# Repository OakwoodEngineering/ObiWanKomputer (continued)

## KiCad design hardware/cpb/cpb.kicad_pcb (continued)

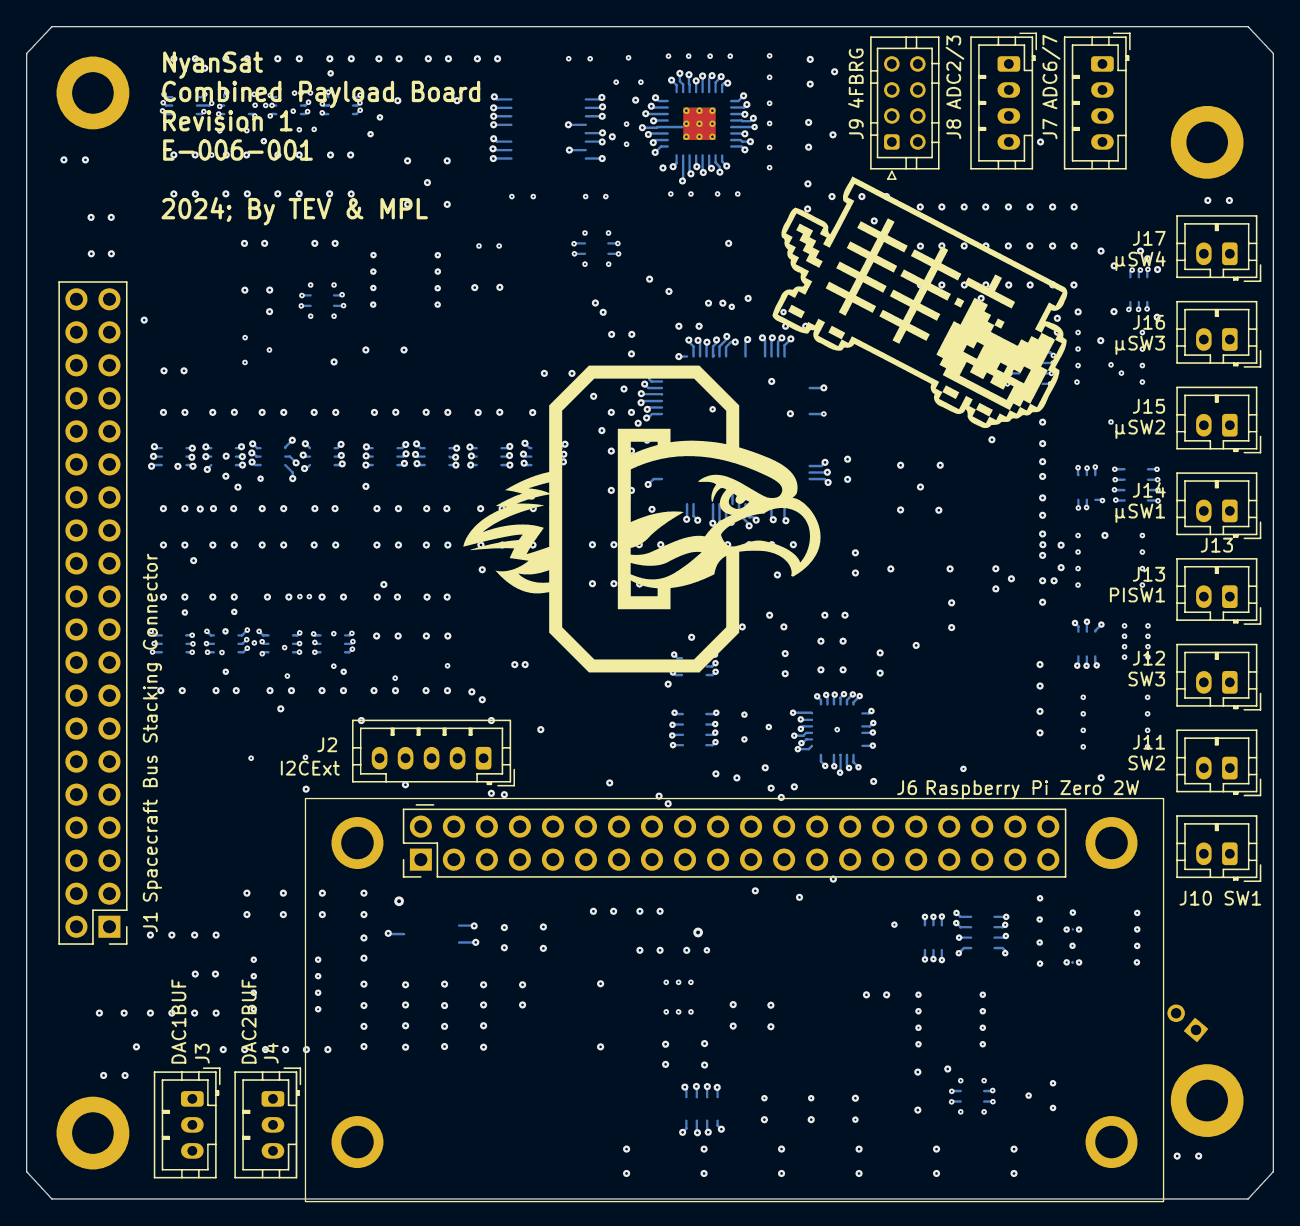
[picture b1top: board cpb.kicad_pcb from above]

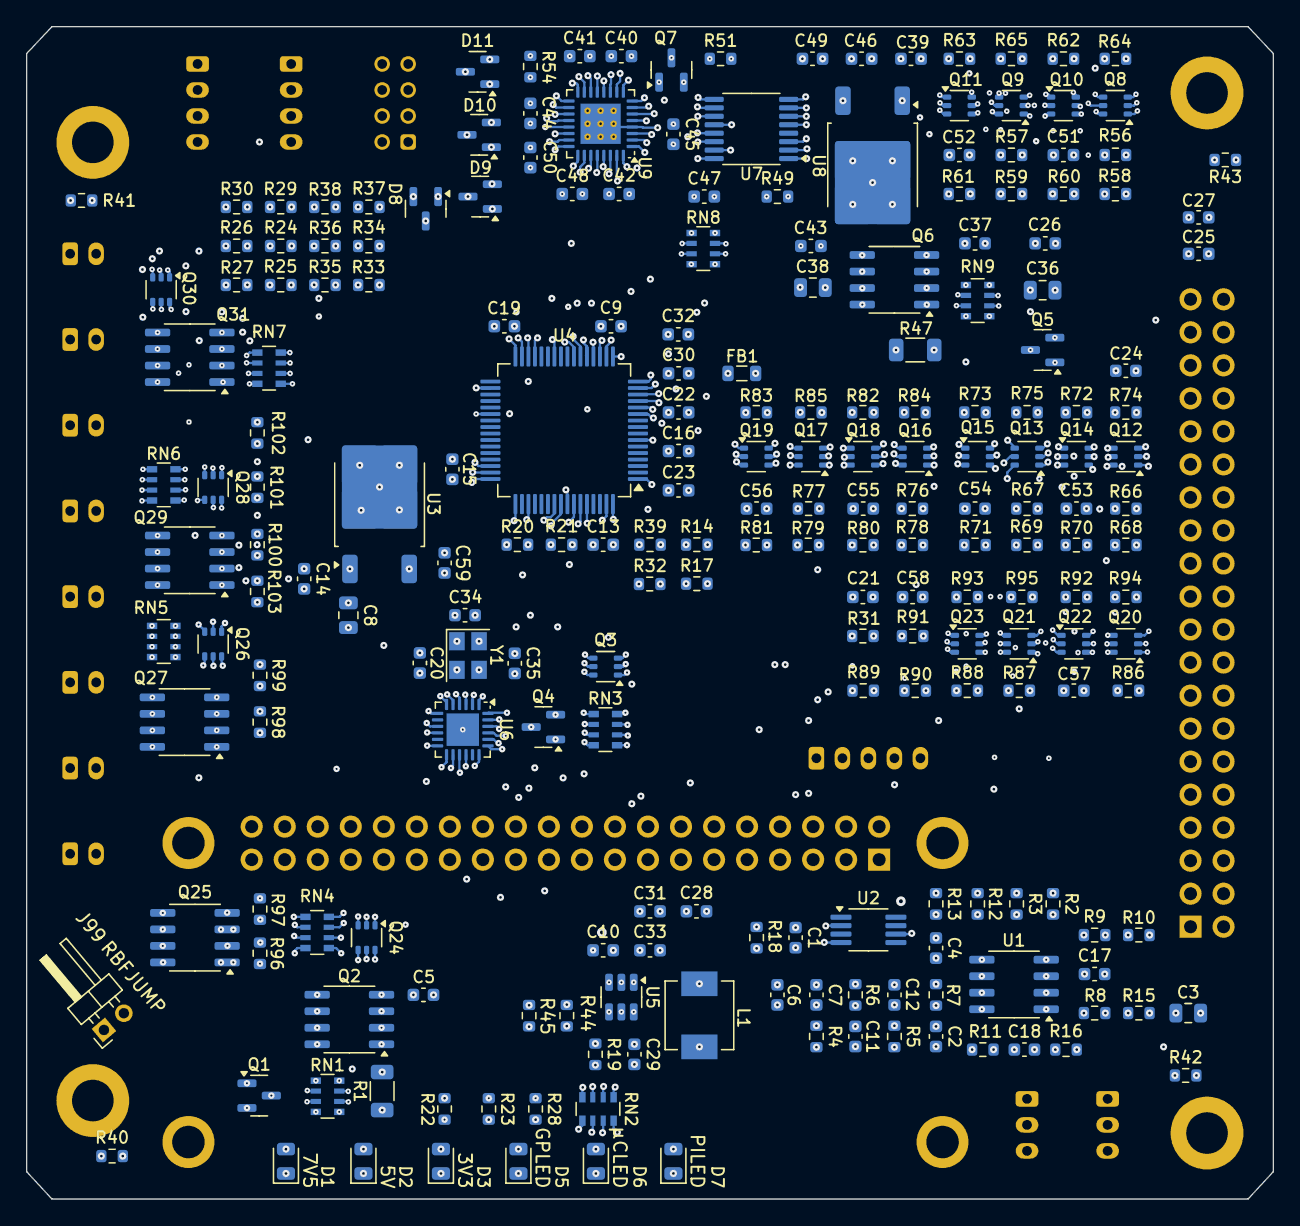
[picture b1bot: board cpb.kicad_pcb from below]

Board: 6 copper layers, 95.9 x 90.2 mm, 239 parts (219 on the bottom side), 178 nets.

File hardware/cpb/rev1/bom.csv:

Designator,Footprint,Quantity,Value,LCSC Part #
"C1, C13, C14, C15, C16, C19, C2, C20, C21, C22, C23, C24, C25, C26, C27, C29, C30, C33, C4, C40, C41, C42, C43, C45, C46, C47, C49, C59, C9",0603,29,100nF,C77055
"C10, C28, C31, C32, C37, C39, C44, C5",0603,8,2.2uF,C77047
"C11, C12",0603,2,68pF,C513699
"C17, C18",0603,2,10uF,C85713
"C3, C36, C38, C8",0805,4,22uF,C2178186
C34,0603,1,22pF,C326840
C35,0603,1,15pF,C1644
C48,0603,1,1.0uF,C29936
C50,0603,1,22nF,C21122
"C51, C52, C53, C54, C55, C56, C57, C58",0603,8,10nF,C100042
"C6, C7",0603,2,680pF,C30816
D1,0805,1,7V5,C84256
"D10, D11, D8, D9",SOT-23,4,MMBZ15VALT1G,C604793
D2,0805,1,5V,C84256
D3,0805,1,3V3,C84256
D5,0805,1,GPLED,C2296
D6,0805,1,μCLED,C2296
D7,0805,1,PILED,C2296
FB1,0805,1,BLM21BD272SN1L,C85839
J1,PinHeader_2x20_P2.54mm_Vertical,1,Spacecraft Bus Stacking Connector,
J10,JST_PH_B2B-PH-K_1x02_P2.00mm_Vertical,1,SW1,
J11,JST_PH_B2B-PH-K_1x02_P2.00mm_Vertical,1,SW2,
J12,JST_PH_B2B-PH-K_1x02_P2.00mm_Vertical,1,SW3,
J13,JST_PH_B2B-PH-K_1x02_P2.00mm_Vertical,1,PISW1,
J14,JST_PH_B2B-PH-K_1x02_P2.00mm_Vertical,1,μSW1,
J15,JST_PH_B2B-PH-K_1x02_P2.00mm_Vertical,1,μSW2,
J16,JST_PH_B2B-PH-K_1x02_P2.00mm_Vertical,1,μSW3,
J17,JST_PH_B2B-PH-K_1x02_P2.00mm_Vertical,1,μSW4,
J2,JST_PH_B5B-PH-K_1x05_P2.00mm_Vertical,1,I2CExt,
J3,JST_PH_B3B-PH-K_1x03_P2.00mm_Vertical,1,DAC1BUF,
J4,JST_PH_B3B-PH-K_1x03_P2.00mm_Vertical,1,DAC2BUF,
J6,RPI02W,1,Raspberry Pi Zero 2W,
J7,JST_PH_B4B-PH-K_1x04_P2.00mm_Vertical,1,ADC6/7,
J8,JST_PH_B4B-PH-K_1x04_P2.00mm_Vertical,1,ADC2/3,
J9,JST_PHD_B8B-PHDSS_2x04_P2.00mm_Vertical,1,4FBRG,
J99,PinHeader_1x02_P2.00mm_Horizontal,1,RBFJUMP,
L1,L_Vishay_IHLP-2020,1,4.7uH,C844991
"Q1, Q4, Q5, Q7",SOT-23,4,PMBT2222A,C23869 
"Q10, Q11, Q14, Q15, Q18, Q19, Q22, Q23",SOT-363_SC-70-6,8,"BSS138PS,115",C193381
"Q12, Q13, Q16, Q17, Q20, Q21, Q24, Q26, Q28, Q3, Q30, Q8, Q9",SOT-363_SC-70-6,13,MBT2222ADW1T1,C157366
"Q2, Q6",SOIC-8_3.9x4.9mm_P1.27mm,2,IRF9393,C520642
"Q25, Q27, Q29, Q31",SOIC-8_3.9x4.9mm_P1.27mm,4,IRF7306,C537809 
"R1, R47",2010,2,200m 1W,C2073579
"R10, R13, R22, R4, R45, R6",0603,6,5.6k,C416722
"R100, R101, R102, R103, R19, R31, R32, R39, R49, R51, R58, R59, R68, R69, R78, R79, R88, R89, R96, R97, R98, R99",0603,22,10k,C844918
"R11, R15, R16, R8",0603,4,0,C122704
"R12, R2, R23, R3, R9",0603,5,3.3k,C844928
"R14, R28",0603,2,1.5k,C844921
"R17, R54",0603,2,15k,C844742
"R18, R29, R30, R37, R38",0603,5,33,C844553
"R20, R21",0603,2,4.7k,C844931
"R24, R25, R26, R27, R33, R34, R35, R36, R40, R41, R42, R43",0603,12,DNP,
R44,0603,1,30k,C844774
"R5, R7",0603,2,9.1k,C491147
"R56, R57, R66, R67, R76, R77, R86, R87",0603,8,680,C23228
"R60, R61, R70, R71, R80, R81, R90, R91",0603,8,100k,C189597
"R62, R63, R72, R73, R82, R83, R92, R93",0603,8,200k,C118142
"R64, R65, R74, R75, R84, R85, R94, R95",0603,8,6.8k,C844805
"RN1, RN3, RN4, RN5, RN6, RN7, RN8, RN9",R_Array_Convex_4x0603,8,4.7k,C327044
RN2,R_Array_Convex_4x0603,1,1.5k,C723702
U1,SOIC-8_3.9x4.9mm_P1.27mm,1,TS912,C73655
U2,MSOP-8_3x3mm_P0.65mm,1,ADR420ARMZ,C208143
"U3, U8",TO-252-2,2,KF33BDT,C283274 
U4,LQFP-64_10x10mm_P0.5mm,1,STM32L072R_B-Z_Tx,C915968
U5,TSOT-23-6,1,AP62301WU,C3194340
U6,HVQFN-24-1EP_4x4mm_P0.5mm_EP2.5x2.5mm,1,SC16IS750xBS,C2651891 
U7,TSSOP-16_4.4x5mm_P0.65mm,1,SC18IS606,C5190384
U9,QFN-32-1EP_5x5mm_P0.5mm_EP3.1x3.1mm_ThermalVias,1,MAX22200,C2845158
Y1,Crystal_SMD_3225-4Pin_3.2x2.5mm,1,14.7456MHz,C2450973

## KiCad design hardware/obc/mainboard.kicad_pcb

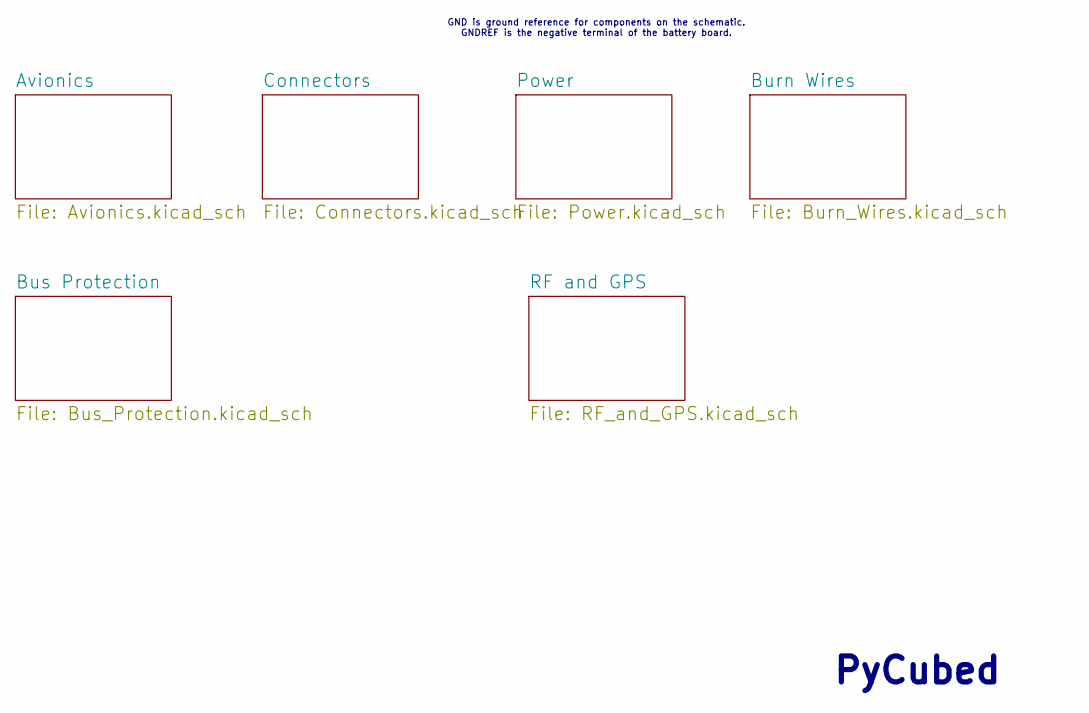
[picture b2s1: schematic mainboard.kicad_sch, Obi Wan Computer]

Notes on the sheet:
GND is ground reference for components on the schematic. GNDREF is the negative terminal of the battery board.
PyCubed

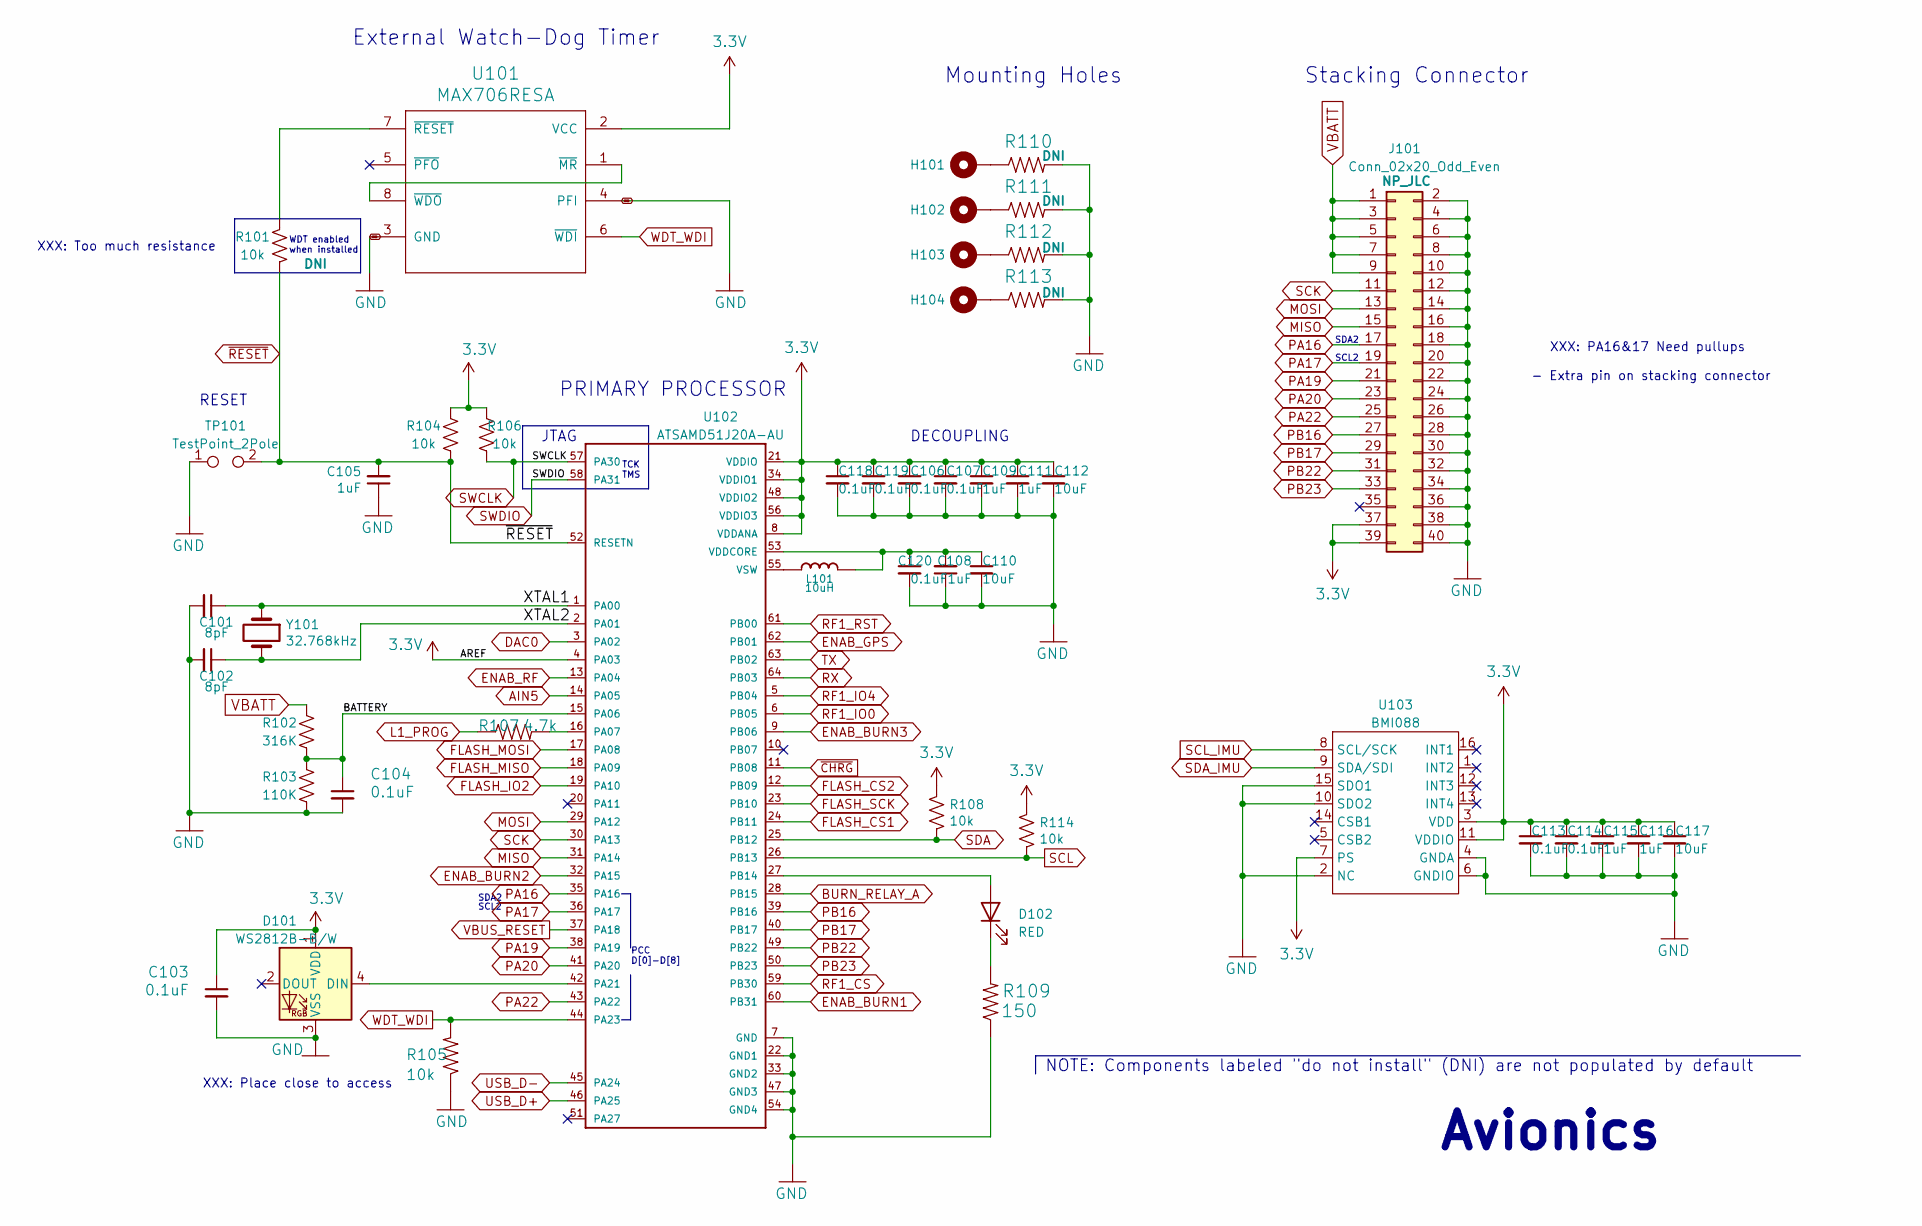
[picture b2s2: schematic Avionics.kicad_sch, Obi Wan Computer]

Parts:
C101, C102: 8pF; C_0603_1608Metric; Manufacturer_Part_Number CC0603JRNPO9BN8R0; LCSC C1882476
C103, C104, C106, C107, C113, C114, C118, C119, C120: 0.1uF; C_0603_1608Metric; Manufacturer_Part_Number CL10B104KB8NNNC; LCSC C1591
C105, C108, C109, C111, C115, C116: 1uF; C_0603_1608Metric; Manufacturer_Part_Number CL10B105KO8NNNC; LCSC C59782
C110, C112, C117: 10uF; C_0603_1608Metric; Manufacturer_Part_Number CL10A106MP8NNNC; LCSC C85713
D101: WS2812B-B/W; LED_WS2812B_PLCC4_5.0x5.0mm_P3.2mm; Manufacturer_Part_Number WS2812B-B/W; LCSC C114586
D102: RED; LED_0805_2012Metric; Manufacturer_Part_Number 17-215SURC/S530-A2/TR8; LCSC C142306
H101, H102, H103, H104: MountingHole_Pad; MountingHole_3.2mm_M3_DIN965_Pad
J101: Conn_02x20_Odd_Even; PinHeader_2x20_P2.54mm_Vertical
L101: 10uH; Sunlord_0805_3.0x3.0mm; Manufacturer_Part_Number SPH3012H100MT; LCSC C370419
R101, R104, R105, R106, R108, R114: 10k; R_0603_1608Metric; Manufacturer_Part_Number ERJ3GEYJ103V; LCSC C169849
R102: 316K; R_0603_1608Metric; Manufacturer_Part_Number CRCW0603316KFKEA; LCSC C844550
R103: 110K; R_0603_1608Metric; Manufacturer_Part_Number RC0603FR-07110KL; LCSC C137807
R107: 4.7k; R_0603_1608Metric; Manufacturer_Part_Number 0603WAF4701T5E; LCSC C23162
R109: 150; R_0603_1608Metric; Manufacturer_Part_Number ERJ3RBD1500V; LCSC C336847
R110, R111, R112, R113: DNI; R_0603_1608Metric
TP101: TestPoint_2Pole; TestPoint_2Pads_Pitch2.54mm_Drill0.8mm
U101: MAX706RESA; SO-8_3.9x4.9mm_P1.27mm; Manufacturer_Part_Number MAX706RESA; LCSC C28380
U102: ATSAMD51J20A-AU; TQFP-64_10x10mm_P0.5mm; Manufacturer_Part_Number ATSAMD51J20A-AU; LCSC C619371
U103: BMI088; LGA-16_4.5x3.0mm_P0.5mm; Manufacturer_Part_Number BMI088
Y101: 32.768kHz; Crystal_SMD_3215-2Pin_3.2x1.5mm; Manufacturer_Part_Number SC-32S32.768kHz20PPM7pF; LCSC C32346

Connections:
3.3V: C103.1, C106.1, C107.1, C109.1, C111.1, C112.1, C113.1, C114.1, C115.1, C116.1, C117.1, C118.1, C119.1, D101.1 (VDD), J101.37, J101.39, R104.1, R106.1, R108.1, R114.1, U101.2 (VCC), U102.4 (PA03), U102.8 (VDDANA), U102.21 (VDDIO), U102.34 (VDDIO1), U102.48 (VDDIO2), U102.56 (VDDIO3), U103.3 (VDD), U103.7 (PS), U103.11 (VDDIO); also elsewhere on the board
/Avionics/BATTERY: C104.1, R102.2, R103.2, U102.15 (PA06)
/Avionics/XTAL1: C101.1, U102.1 (PA00), Y101.1
/Avionics/XTAL2: C102.1, U102.2 (PA01), Y101.2
AIN5: U102.14 (PA05); also elsewhere on the board
BURN_RELAY_A: U102.28 (PB15); also elsewhere on the board
DAC0: U102.3 (PA02)
ENAB_BURN1: U102.60 (PB31); also elsewhere on the board
ENAB_BURN2: U102.32 (PA15); also elsewhere on the board
ENAB_BURN3: U102.9 (PB06); also elsewhere on the board
ENAB_GPS: U102.62 (PB01); also elsewhere on the board
ENAB_RF: U102.13 (PA04); also elsewhere on the board
FLASH_CS1: U102.24 (PB11); also elsewhere on the board
FLASH_CS2: U102.12 (PB09); also elsewhere on the board
FLASH_IO2: U102.19 (PA10); also elsewhere on the board
FLASH_MISO: U102.18 (PA09); also elsewhere on the board
FLASH_MOSI: U102.17 (PA08); also elsewhere on the board
FLASH_SCK: U102.23 (PB10); also elsewhere on the board
GND: C101.2, C102.2, C103.2, C104.2, C105.1, C106.2, C107.2, C108.1, C109.2, C110.2, C111.2, C112.2, C113.2, C114.2, C115.2, C116.2, C117.2, C118.2, C119.2, C120.2, D101.3 (VSS), J101.2, J101.4, J101.6, J101.8, J101.10, J101.12, J101.14, J101.16, J101.18, J101.20, J101.22, J101.24, J101.26, J101.28, J101.30, J101.32, J101.34, J101.36, J101.38, J101.40, R103.1, R105.1, R109.1, R110.2, R111.2, R112.2, R113.2, TP101.1, U101.3 (GND), U101.4 (PFI), U102.7 (GND), U102.22 (GND1), U102.33 (GND2), U102.47 (GND3), U102.54 (GND4), U103.2 (NC), U103.4 (GNDA), U103.6 (GNDIO), U103.10 (SDO2), U103.15 (SDO1); also elsewhere on the board
L1_PROG: R107.1; also elsewhere on the board
MISO: J101.15, U102.31 (PA14); also elsewhere on the board
MOSI: J101.13, U102.29 (PA12); also elsewhere on the board
unnamed: D101.4 (DIN), U102.42 (PA21)
unnamed: D102.2 (A), U102.27 (PB14)
unnamed: D102.1 (K), R109.2
unnamed: H101.1, R110.1
unnamed: H102.1, R111.1
unnamed: H103.1, R112.1
unnamed: H104.1, R113.1
unnamed: U101.1 (~MR), U101.8 (~WDO)
unnamed: R101.2, U101.7 (~RESET)
unnamed: R107.2, U102.16 (PA07)
unnamed: C108.2, C110.1, C120.1, L101.1, U102.53 (VDDCORE)
unnamed: L101.2, U102.55 (VSW)
PA16: J101.17, U102.35 (PA16)
PA17: J101.19, U102.36 (PA17)
PA19: J101.21, U102.38 (PA19)
PA20: J101.23, U102.41 (PA20)
PA22: J101.25, U102.43 (PA22)
PB16: J101.27, U102.39 (PB16)
PB17: J101.29, U102.40 (PB17)
PB22: J101.31, U102.49 (PB22)
PB23: J101.33, U102.50 (PB23)
RF1_CS: U102.59 (PB30); also elsewhere on the board
RF1_IO0: U102.6 (PB05); also elsewhere on the board
RF1_IO4: U102.5 (PB04); also elsewhere on the board
RF1_RST: U102.61 (PB00); also elsewhere on the board
RX: U102.64 (PB03); also elsewhere on the board
SCK: J101.11, U102.30 (PA13); also elsewhere on the board
SCL: R114.2, U102.26 (PB13); also elsewhere on the board
SCL_IMU: U103.8 (SCL/SCK); also elsewhere on the board
SDA: R108.2, U102.25 (PB12); also elsewhere on the board
SDA_IMU: U103.9 (SDA/SDI); also elsewhere on the board
SWCLK: R106.2, U102.57 (PA30); also elsewhere on the board
SWDIO: U102.58 (PA31); also elsewhere on the board
TX: U102.63 (PB02); also elsewhere on the board
USB_D+: U102.46 (PA25); also elsewhere on the board
USB_D-: U102.45 (PA24); also elsewhere on the board
VBATT: J101.1, J101.3, J101.5, J101.7, J101.9, R102.1; also elsewhere on the board
VBUS_RESET: U102.37 (PA18); also elsewhere on the board
WDT_WDI: R105.2, U101.6 (~WDI), U102.44 (PA23)
~CHRG: U102.11 (PB08); also elsewhere on the board
~RESET: C105.2, R101.1, R104.2, TP101.2, U102.52 (RESETN); also elsewhere on the board

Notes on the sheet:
WDT enabled when installed
Mounting Holes
NOTE: Components labeled "do not install" (DNI) are not populated by default
Avionics
XXX: PA16&17 Need pullups - Extra pin on stacking connector
XXX: Place close to access
XXX: Too much resistance
TCK TMS
RESET
SDA2
External Watch-Dog Timer
SCL2
PCC D[0]-D[8]
DECOUPLING
JTAG
PRIMARY PROCESSOR
Stacking Connector

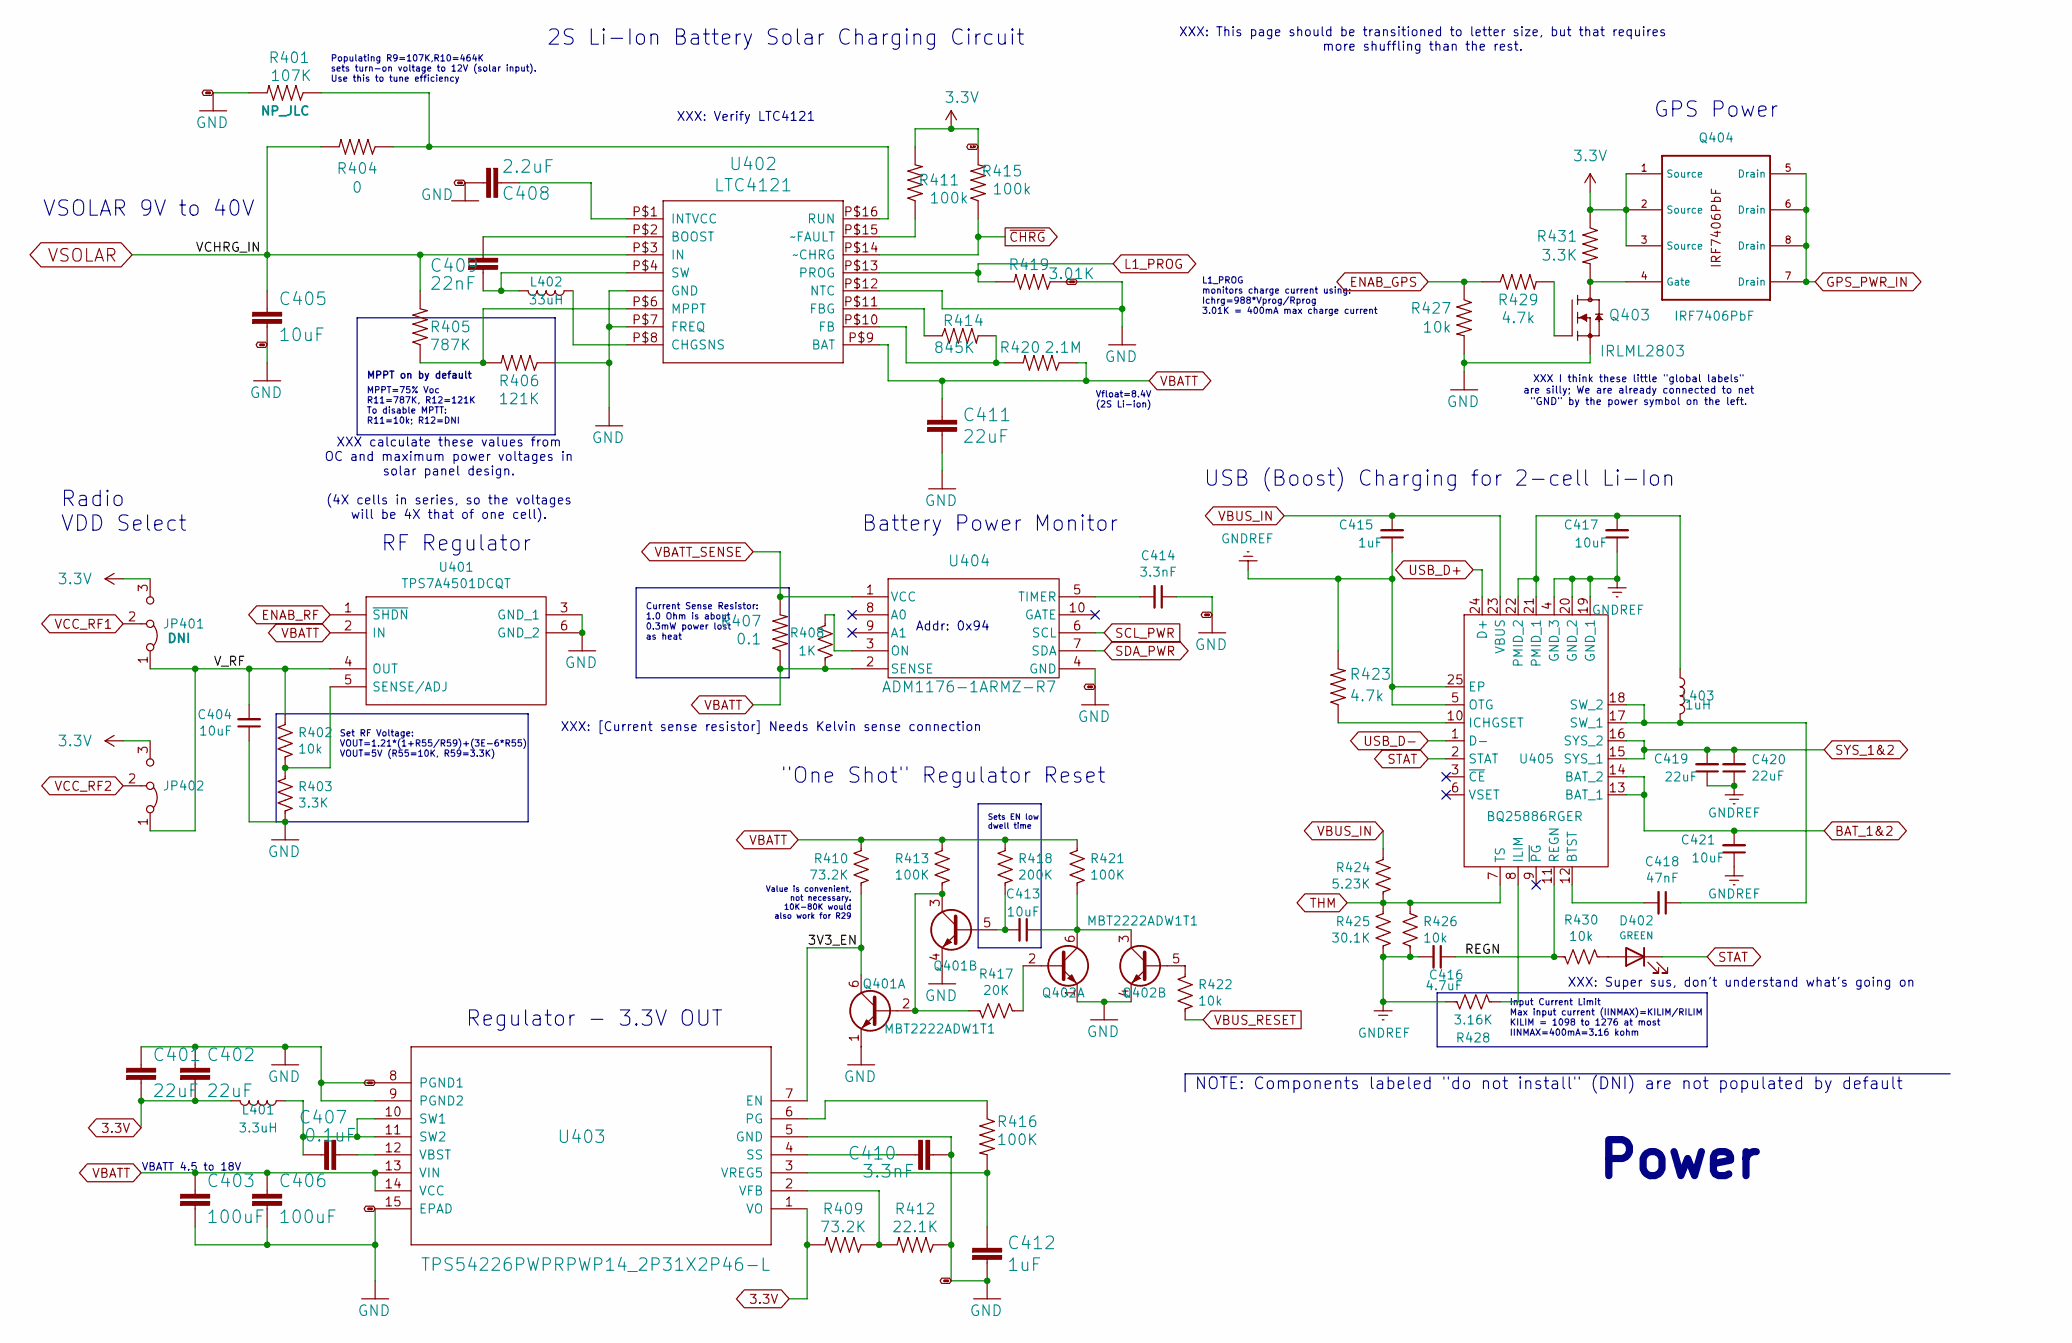
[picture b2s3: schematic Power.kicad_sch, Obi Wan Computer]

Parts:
C401, C402, C411, C419, C420: 22uF; C_0603_1608Metric; Manufacturer_Part_Number GRM188R61A226ME15D; LCSC C84419
C403, C406: 100uF; C_1210_3225Metric; Manufacturer_Part_Number EMK325ABJ107MM-P; LCSC C90143
C404, C405, C413, C417, C421: 10uF; C_0603_1608Metric; Manufacturer_Part_Number CL10A106MP8NNNC; LCSC C85713
C407: 0.1uF; C_0603_1608Metric; Manufacturer_Part_Number CL10B104KB8NNNC; LCSC C1591
C408: 2.2uF; C_0603_1608Metric; Manufacturer_Part_Number CL10A225KO8NNNC; LCSC C23630
C409: 22nF; C_0603_1608Metric; Manufacturer_Part_Number CL10B223KB8NNNC; LCSC C21122
C410, C414: 3.3nF; C_0603_1608Metric; Manufacturer_Part_Number CL10B332KB8NNNC; LCSC C1613
C412, C415: 1uF; C_0603_1608Metric; Manufacturer_Part_Number CL10B105KO8NNNC; LCSC C59782
C416: 4.7uF; C_0603_1608Metric; Manufacturer_Part_Number CL10A475KP8NNNC; LCSC C1705
C418: 47nF; C_0603_1608Metric; Manufacturer_Part_Number CL10B473KB8NNNC; LCSC C1622
D402: GREEN; LED_0805_2012Metric; Manufacturer_Part_Number KT-0805G; LCSC C2297
JP401, JP402: Jumper_3_Bridged12; SolderJumper-3_P1.3mm_Bridged12_RoundedPad1.0x1.5mm
L401: 3.3uH; TDK_1008_2.9x2.0mm; Manufacturer_Part_Number TFM252012ALMA3R3MTAA; LCSC C404805
L402: 33uH; TDK_1008_4.9x5.5mm; Manufacturer_Part_Number VLCF5024T-330MR50-2; LCSC C2046704
L403: 1uH; L_1008_2520Metric; Manufacturer_Part_Number DFE2HCAH1R0MJ0L; LCSC C5247968
Q401, Q402: MBT2222ADW1T1; SOT-363_SC-70-6; Manufacturer_Part_Number MBT2222ADW1T1G; LCSC C157366
Q403: IRLML2803; SOT-23; Manufacturer_Part_Number IRLML2803TRPBF; LCSC C2590
Q404: IRF7406PbF; SO-8_3.9x4.9mm_P1.27mm; Manufacturer_Part_Number IRF7406TRPBF; LCSC C169769
R401: 107K; R_0603_1608Metric
R402, R422, R426, R427, R430: 10k; R_0603_1608Metric; Manufacturer_Part_Number ERJ3GEYJ103V; LCSC C169849
R403, R431: 3.3K; R_0603_1608Metric; Manufacturer_Part_Number CRCW06033K30JNEA; LCSC C844782
R404: 0; R_0603_1608Metric; Manufacturer_Part_Number MCT06030Z0000ZP500; LCSC C2654002
R405: 787K; R_0603_1608Metric; Manufacturer_Part_Number RC0603FR-07787KL; LCSC C246008
R406: 121K; R_0603_1608Metric; Manufacturer_Part_Number RT0603BRD07121KL; LCSC C861095
R407: 0.1; R_2512_6332Metric; LCSC C165698
R408: 1K; R_0603_1608Metric; Manufacturer_Part_Number CRCW06031K00FKEAC; LCSC C844746
R409, R410: 73.2K; R_0603_1608Metric; Manufacturer_Part_Number CRCW060373K2FKEA; LCSC C843966
R411, R415: 100k; R_0603_1608Metric; Manufacturer_Part_Number CRCW0603100KFKEC; LCSC C5369222
R412: 22.1K; R_0603_1608Metric; Manufacturer_Part_Number AF0603FR-0722K1L; LCSC C2838732
R413, R416, R421: 100K; R_0603_1608Metric; Manufacturer_Part_Number CRCW0603100KFKEC; LCSC C5369222
R414: 845K; R_0603_1608Metric; Manufacturer_Part_Number CRCW0603845KFKEA; LCSC C2091473
R417: 20K; R_0603_1608Metric; Manufacturer_Part_Number CRCW060320K0FKEC; LCSC C2076573
R418: 200K; R_0603_1608Metric; Manufacturer_Part_Number ERA3AEB204V; LCSC C473261
R419: 3.01K; R_0603_1608Metric; Manufacturer_Part_Number TNPW06033K01BEEA; LCSC C2075334
R420: 2.1M; R_0603_1608Metric; Manufacturer_Part_Number CRCW06032M10FKEA; LCSC C2085910
R423, R429: 4.7k; R_0603_1608Metric; Manufacturer_Part_Number 0603WAF4701T5E; LCSC C23162
R424: 5.23K; R_0603_1608Metric; Manufacturer_Part_Number AC0603FR-075K23L; LCSC C227977
R425: 30.1K; R_0603_1608Metric; Manufacturer_Part_Number RC0603FR-0730K1L; LCSC C137745
R428: 3.16K; R_0603_1608Metric; Manufacturer_Part_Number RC0603FR-073K16L; LCSC C185333
U401: TPS7A4501DCQT; SOT-223-6; Manufacturer_Part_Number TPS7A4501DCQT; LCSC C2869558
U402: LTC4121; QFN-16-PAD; Manufacturer_Part_Number LTC4121EUD; LCSC C687336
U403: TPS54226PWPRPWP14_2P31X2P46-L; HTSSOP-14-1EP_4.4x5mm_P0.65mm_EP3.4x5mm_Mask3x3.1mm; Manufacturer_Part_Number TPS54226PWPR; LCSC C72066
U404: ADM1176-1ARMZ-R7; Manufacturer_Part_Number ADM1176-1ARMZ-R7; LCSC C657860
U405: BQ25886RGER; QFN50P400X400X100-25N-D; Manufacturer_Part_Number BQ25886RGER; LCSC C2765094

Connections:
3.3V: C401.2, C402.2, JP401.3 (B), JP402.3 (B), L401.2, Q404.1 (Source), Q404.2 (Source), Q404.3 (Source), R409.2, R411.2, R415.2, R431.1, U403.1 (VO); also elsewhere on the board
/Power/3V3_EN: Q401.6 (C1), R410.2, U403.7 (EN)
/Power/REGN: C416.1, R430.2, U405.11 (REGN)
/Power/V_RF: C404.2, JP401.1 (A), JP402.1 (A), R402.1, U401.4 (OUT)
BAT_1&2: C421.2, U405.13 (BAT_1), U405.14 (BAT_2); also elsewhere on the board
ENAB_GPS: R427.1, R429.1; also elsewhere on the board
ENAB_RF: U401.1 (~SHDN); also elsewhere on the board
GND: C401.1, C402.1, C403.2, C404.1, C405.2, C406.2, C408.2, C410.2, C411.2, C412.2, C414.1, Q401.1 (E1), Q401.4 (E2), Q402.1 (E1), Q402.4 (E2), Q403.2 (S), R401.2, R403.2, R406.1, R412.1, R419.1, R427.2, U401.3 (GND_1), U401.6 (GND_2), U402.P$5 (GND), U402.P$7 (FREQ), U402.P$12 (NTC), U402.P$17 (GND), U403.5 (GND), U403.8 (PGND1), U403.9 (PGND2), U403.15 (EPAD), U404.4 (GND); also elsewhere on the board
GNDREF: C415.1, C416.2, C417.1, C419.1, C420.1, C421.1, R423.2, R425.1, R426.1, R428.1, U405.4 (GND_3), U405.5 (OTG), U405.19 (GND_1), U405.20 (GND_2), U405.25 (EP); also elsewhere on the board
GPS_PWR_IN: Q404.5 (Drain), Q404.6 (Drain), Q404.7 (Drain), Q404.8 (Drain); also elsewhere on the board
L1_PROG: R419.2, U402.P$13 (PROG); also elsewhere on the board
unnamed: D402.2 (A), R430.1
unnamed: Q401.2 (B1), Q401.3 (C2), R413.2, R417.2
unnamed: C413.2, Q401.5 (B2), R418.2
unnamed: Q402.2 (B1), R417.1
unnamed: C413.1, Q402.3 (C2), Q402.6 (C1), R421.2
unnamed: Q402.5 (B2), R422.1
unnamed: Q403.3 (D), Q404.4 (Gate), R431.2
unnamed: Q403.1 (G), R429.2
unnamed: R402.2, R403.1, U401.5 (SENSE/ADJ)
unnamed: C409.1, U402.P$2 (BOOST)
unnamed: L402.1, U402.P$8 (CHGSNS)
unnamed: R414.2, R420.2, U402.P$10 (FB)
unnamed: R414.1, U402.P$11 (FBG)
unnamed: C408.1, U402.P$1 (INTVCC)
unnamed: R405.1, R406.2, U402.P$6 (MPPT)
unnamed: R401.1, R404.1, U402.P$16 (RUN)
unnamed: C409.2, L402.2, U402.P$4 (SW)
unnamed: R411.1, U402.P$15 (~FAULT)
unnamed: R416.1, U403.6 (PG)
unnamed: C410.1, U403.4 (SS)
unnamed: C407.1, L401.1, U403.10 (SW1), U403.11 (SW2)
unnamed: C407.2, U403.12 (VBST)
unnamed: R409.1, R412.2, U403.2 (VFB)
unnamed: C412.1, R416.2, U403.3 (VREG5)
unnamed: R408.2, U404.3 (ON)
unnamed: C414.2, U404.5 (TIMER)
unnamed: C418.2, U405.12 (BTST)
unnamed: R423.1, U405.10 (ICHGSET)
unnamed: R428.2, U405.8 (ILIM)
unnamed: C417.2, L403.1, U405.21 (PMID_1), U405.22 (PMID_2)
unnamed: C418.1, L403.2, U405.17 (SW_1), U405.18 (SW_2)
SCL_PWR: U404.6 (SCL); also elsewhere on the board
SDA_PWR: U404.7 (SDA); also elsewhere on the board
STAT: D402.1 (K), U405.2 (STAT)
SYS_1&2: C419.2, C420.2, U405.15 (SYS_1), U405.16 (SYS_2); also elsewhere on the board
THM: R424.2, R425.2, R426.2, U405.7 (TS)
USB_D+: U405.24 (D+); also elsewhere on the board
USB_D-: U405.1 (D-); also elsewhere on the board
VBATT: C403.1, C406.1, C411.1, R407.1, R408.1, R410.1, R413.1, R418.1, R420.1, R421.1, U401.2 (IN), U402.P$9 (BAT), U403.13 (VIN), U403.14 (VCC), U404.2 (SENSE); also elsewhere on the board
VBATT_SENSE: R407.2, U404.1 (VCC); also elsewhere on the board
VBUS_IN: C415.2, R424.1, U405.23 (VBUS); also elsewhere on the board
VBUS_RESET: R422.2; also elsewhere on the board
VCC_RF1: JP401.2 (C); also elsewhere on the board
VCC_RF2: JP402.2 (C)
VSOLAR: C405.1, R404.2, R405.2, U402.P$3 (IN); also elsewhere on the board
~CHRG: R415.1, U402.P$14 (~CHRG); also elsewhere on the board

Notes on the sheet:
Set RF Voltage: VOUT=1.21*(1+R55/R59)+(3E-6*R55) VOUT=5V (R55=10K, R59=3.3K)
MPPT on by default
Sets EN low dwell time
XXX: Super sus, don't understand what's going on
Value is convenient, not necessary. 10K-80K would also work for R29
VBATT 4.5 to 18V
Regulator - 3.3V OUT
Radio VDD Select
Populating R9=107K,R10=464K sets turn-on voltage to 12V (solar input). Use this to tune efficiency
XXX: This page should be transitioned to letter size, but that requires more shuffling than the rest.
RF Regulator
L1_PROG monitors charge current using: Ichrg=988*Vprog/Rprog 3.01K = 400mA max charge current
XXX: Verify LTC4121
XXX calculate these values from OC and maximum power voltages in solar panel design. (4X cells in series, so the voltages will be 4X that of one cell).
VSOLAR 9V to 40V
GPS Power
USB (Boost) Charging for 2-cell Li-Ion
Input Current Limit Max input current (IINMAX)=KILIM/RILIM KILIM = 1098 to 1276 at most IINMAX=400mA=3.16 kohm
NOTE: Components labeled "do not install" (DNI) are not populated by default
Battery Power Monitor
Power
Addr: 0x94
2S Li-Ion Battery Solar Charging Circuit
XXX I think these little "global labels" are silly; We are already connected to net "GND" by the power symbol on the left.
Vfloat=8.4V (2S Li-ion)
XXX: [Current sense resistor] Needs Kelvin sense connection
MPPT=75% Voc R11=787K, R12=121K To disable MPTT: R11=10k; R12=DNI
Current Sense Resistor: 1.0 Ohm is about 0.3mW power lost as heat
"One Shot" Regulator Reset
